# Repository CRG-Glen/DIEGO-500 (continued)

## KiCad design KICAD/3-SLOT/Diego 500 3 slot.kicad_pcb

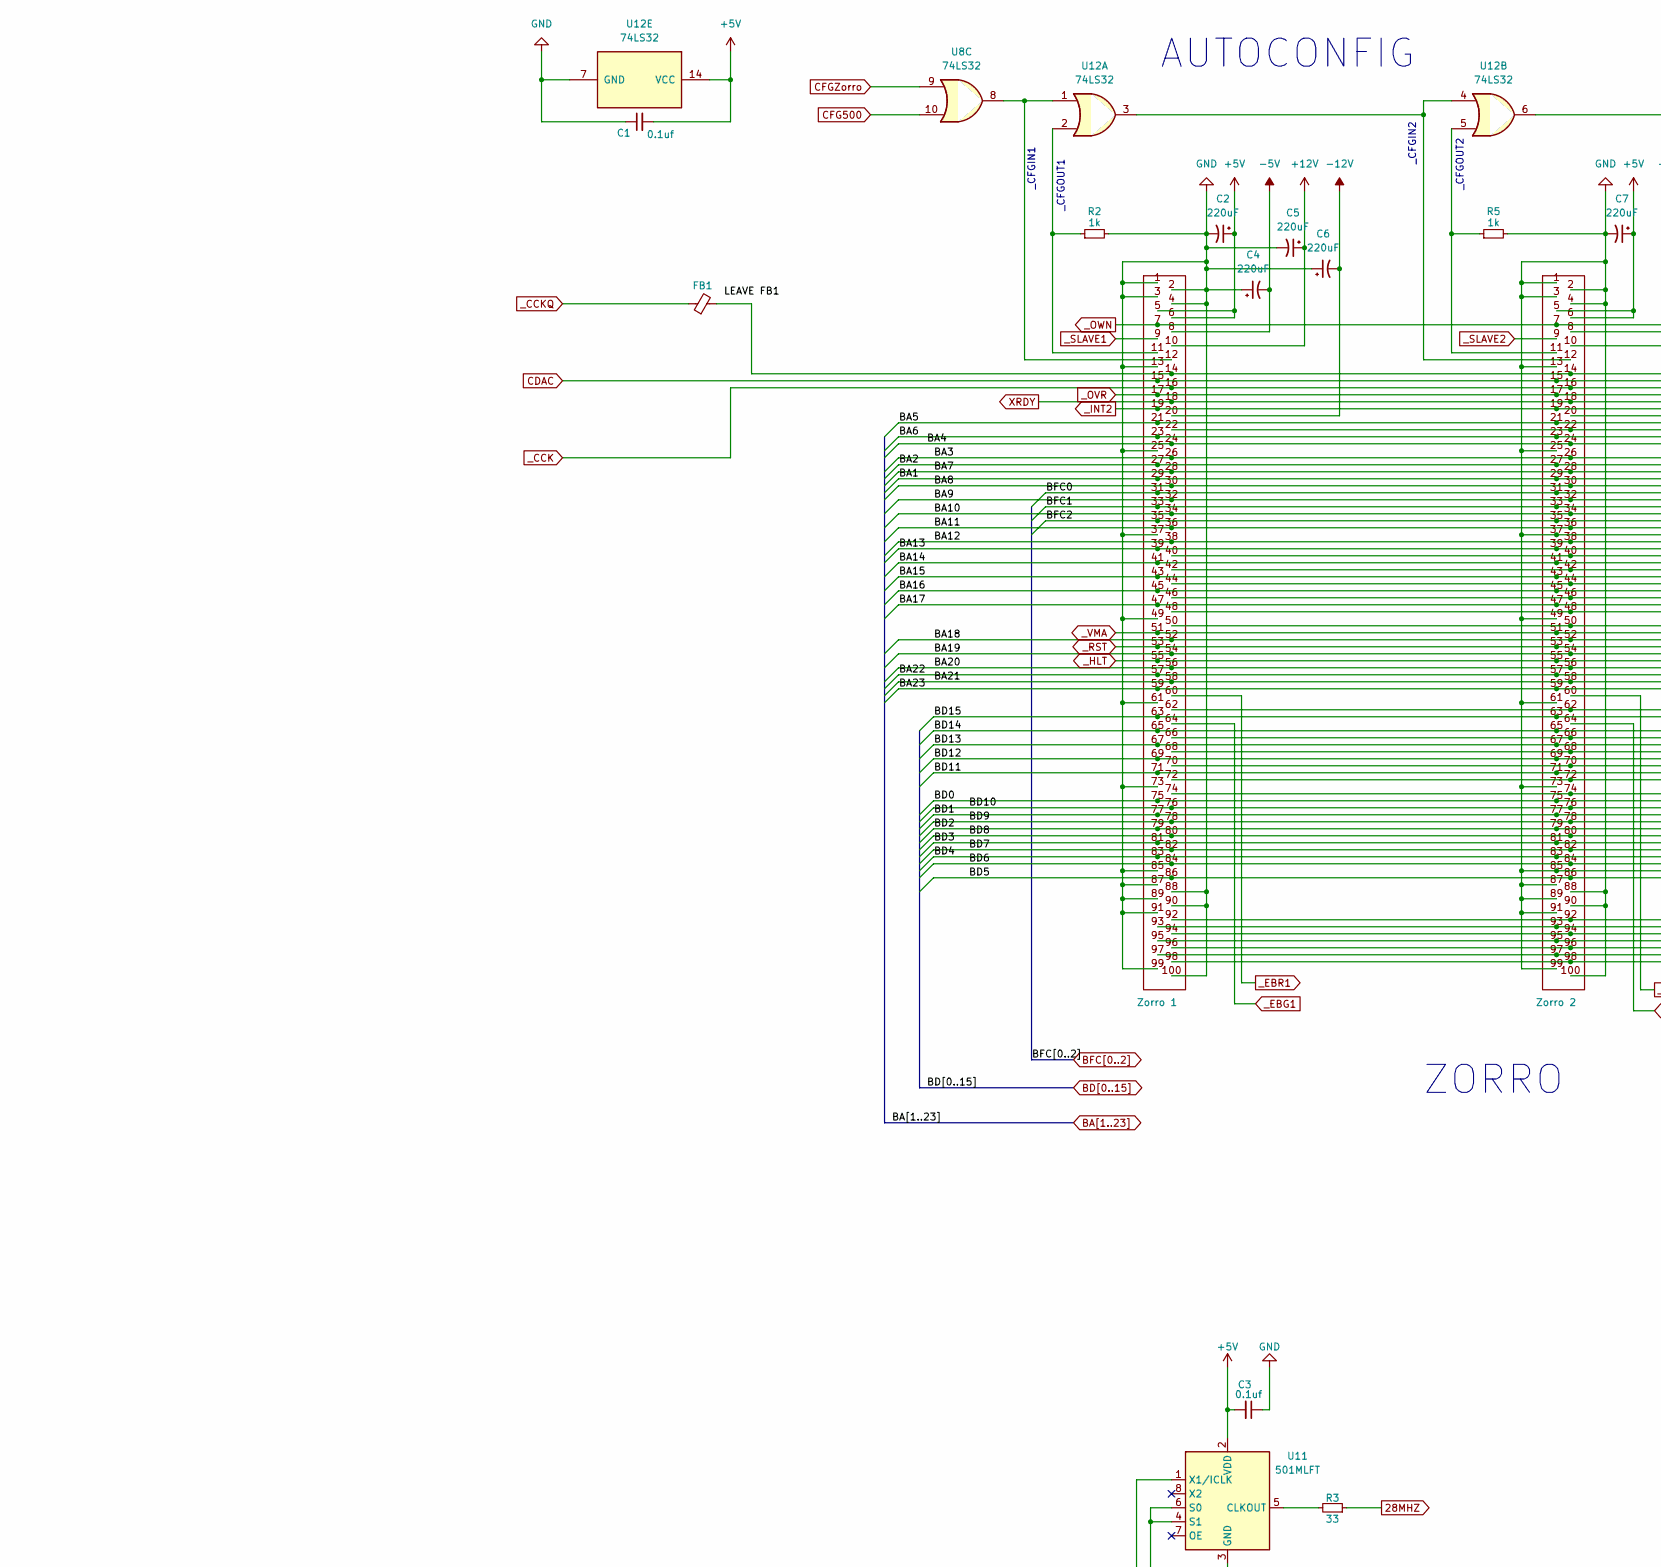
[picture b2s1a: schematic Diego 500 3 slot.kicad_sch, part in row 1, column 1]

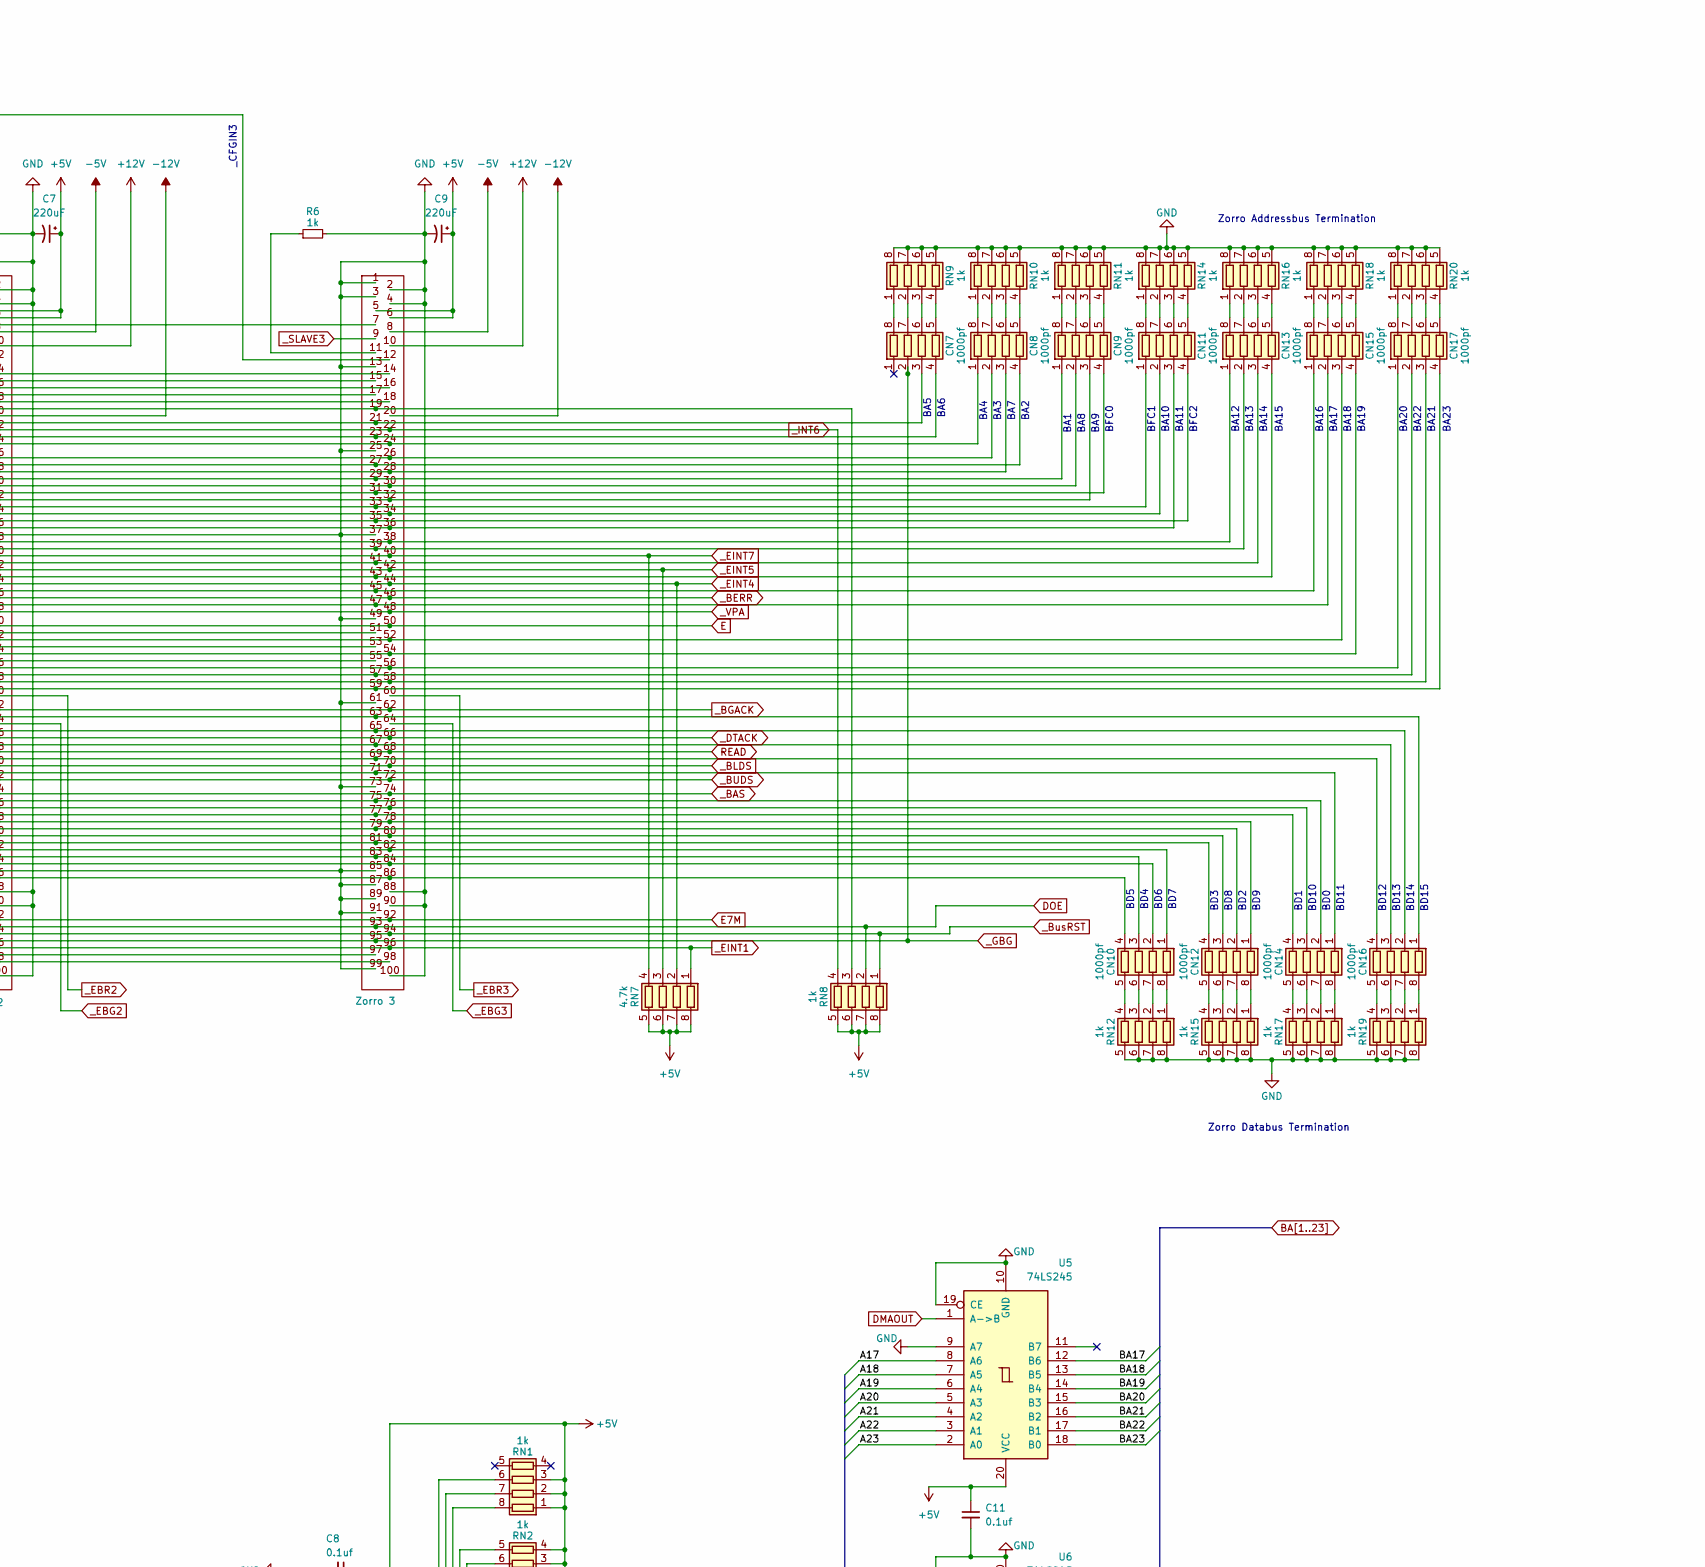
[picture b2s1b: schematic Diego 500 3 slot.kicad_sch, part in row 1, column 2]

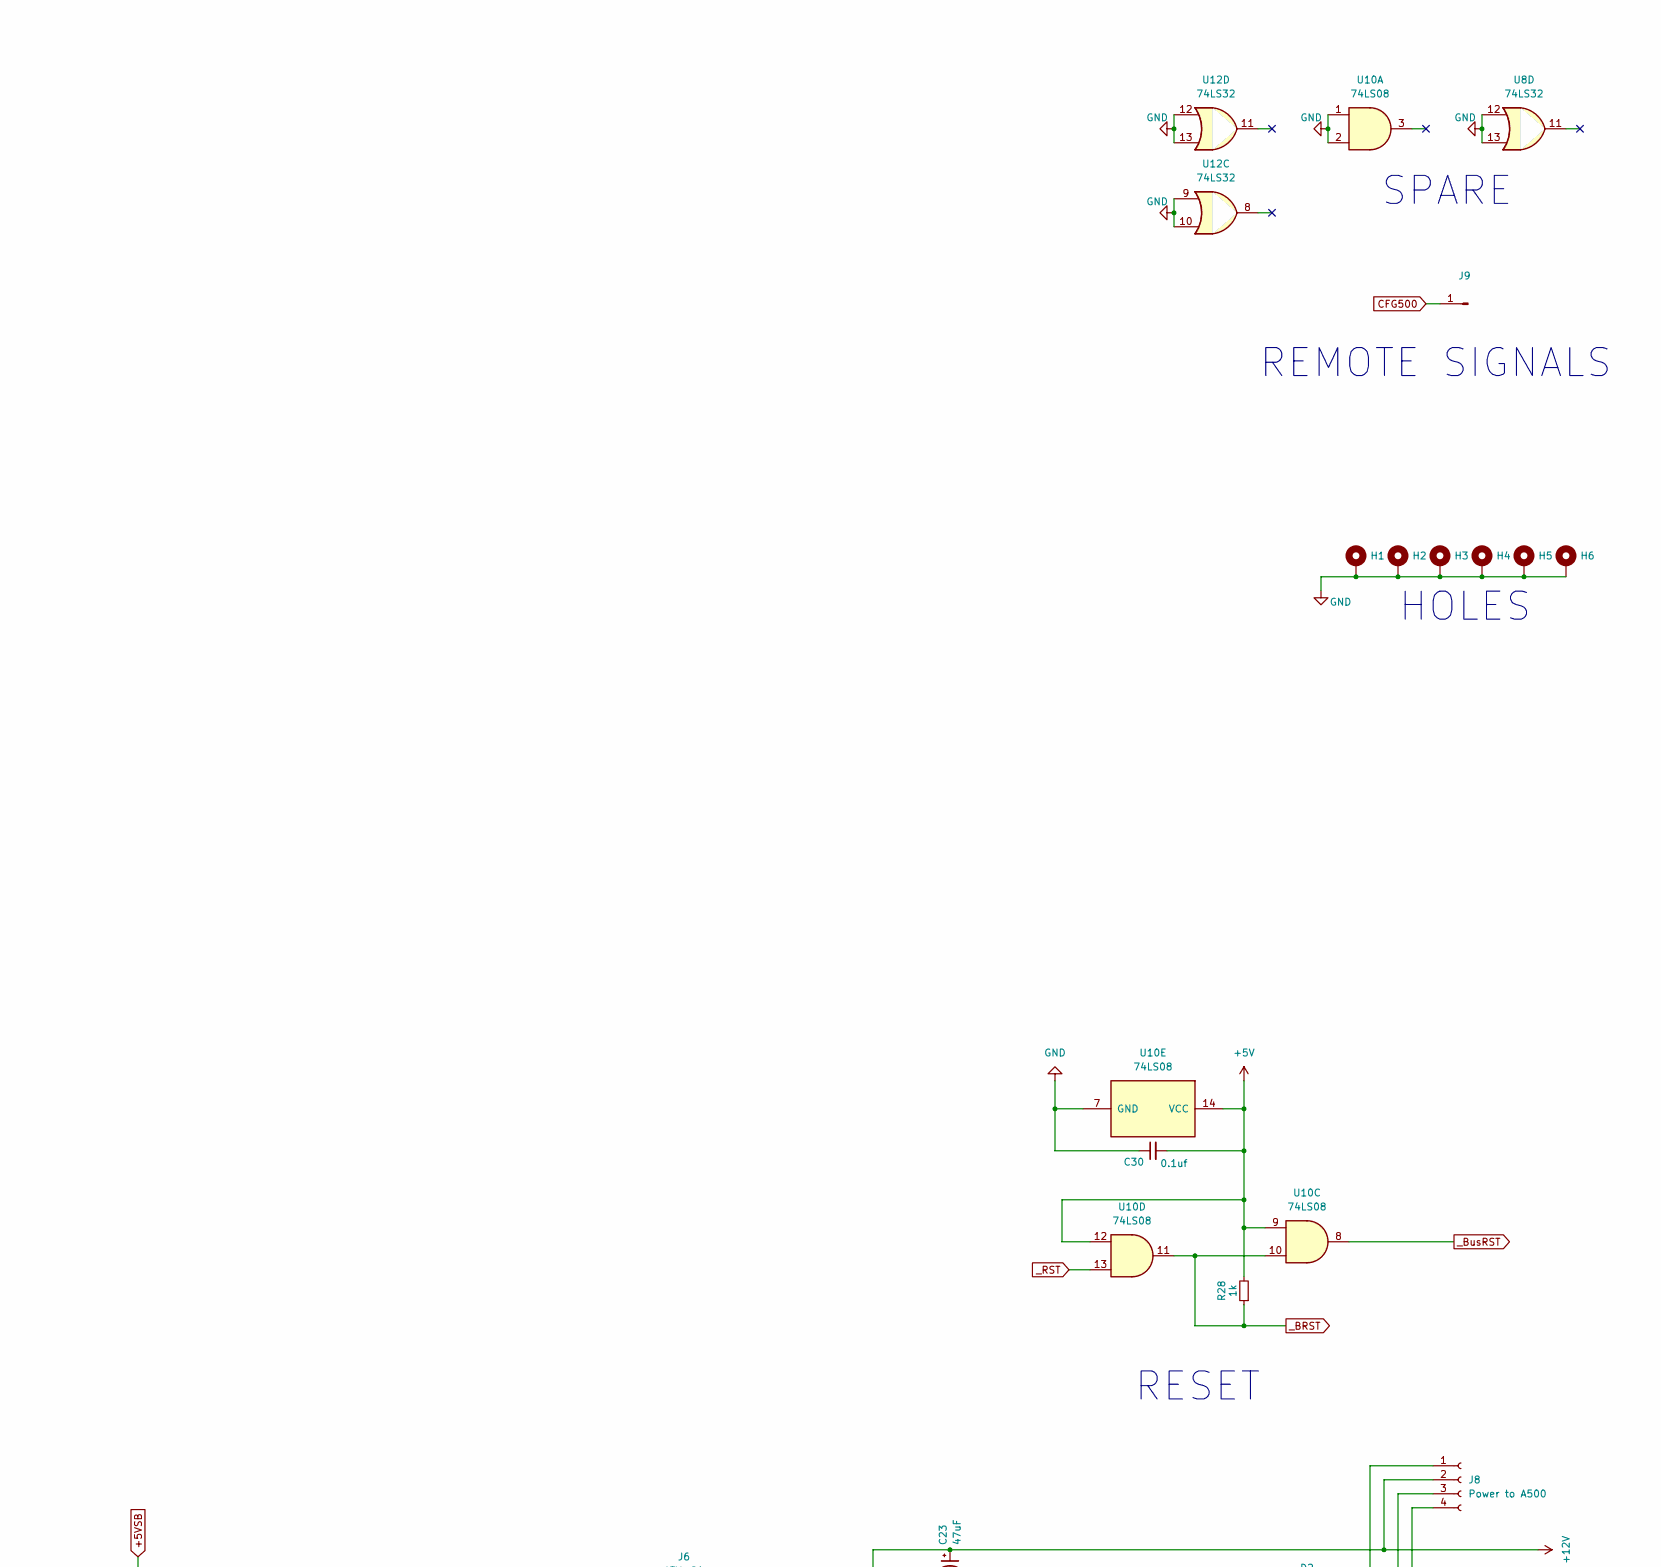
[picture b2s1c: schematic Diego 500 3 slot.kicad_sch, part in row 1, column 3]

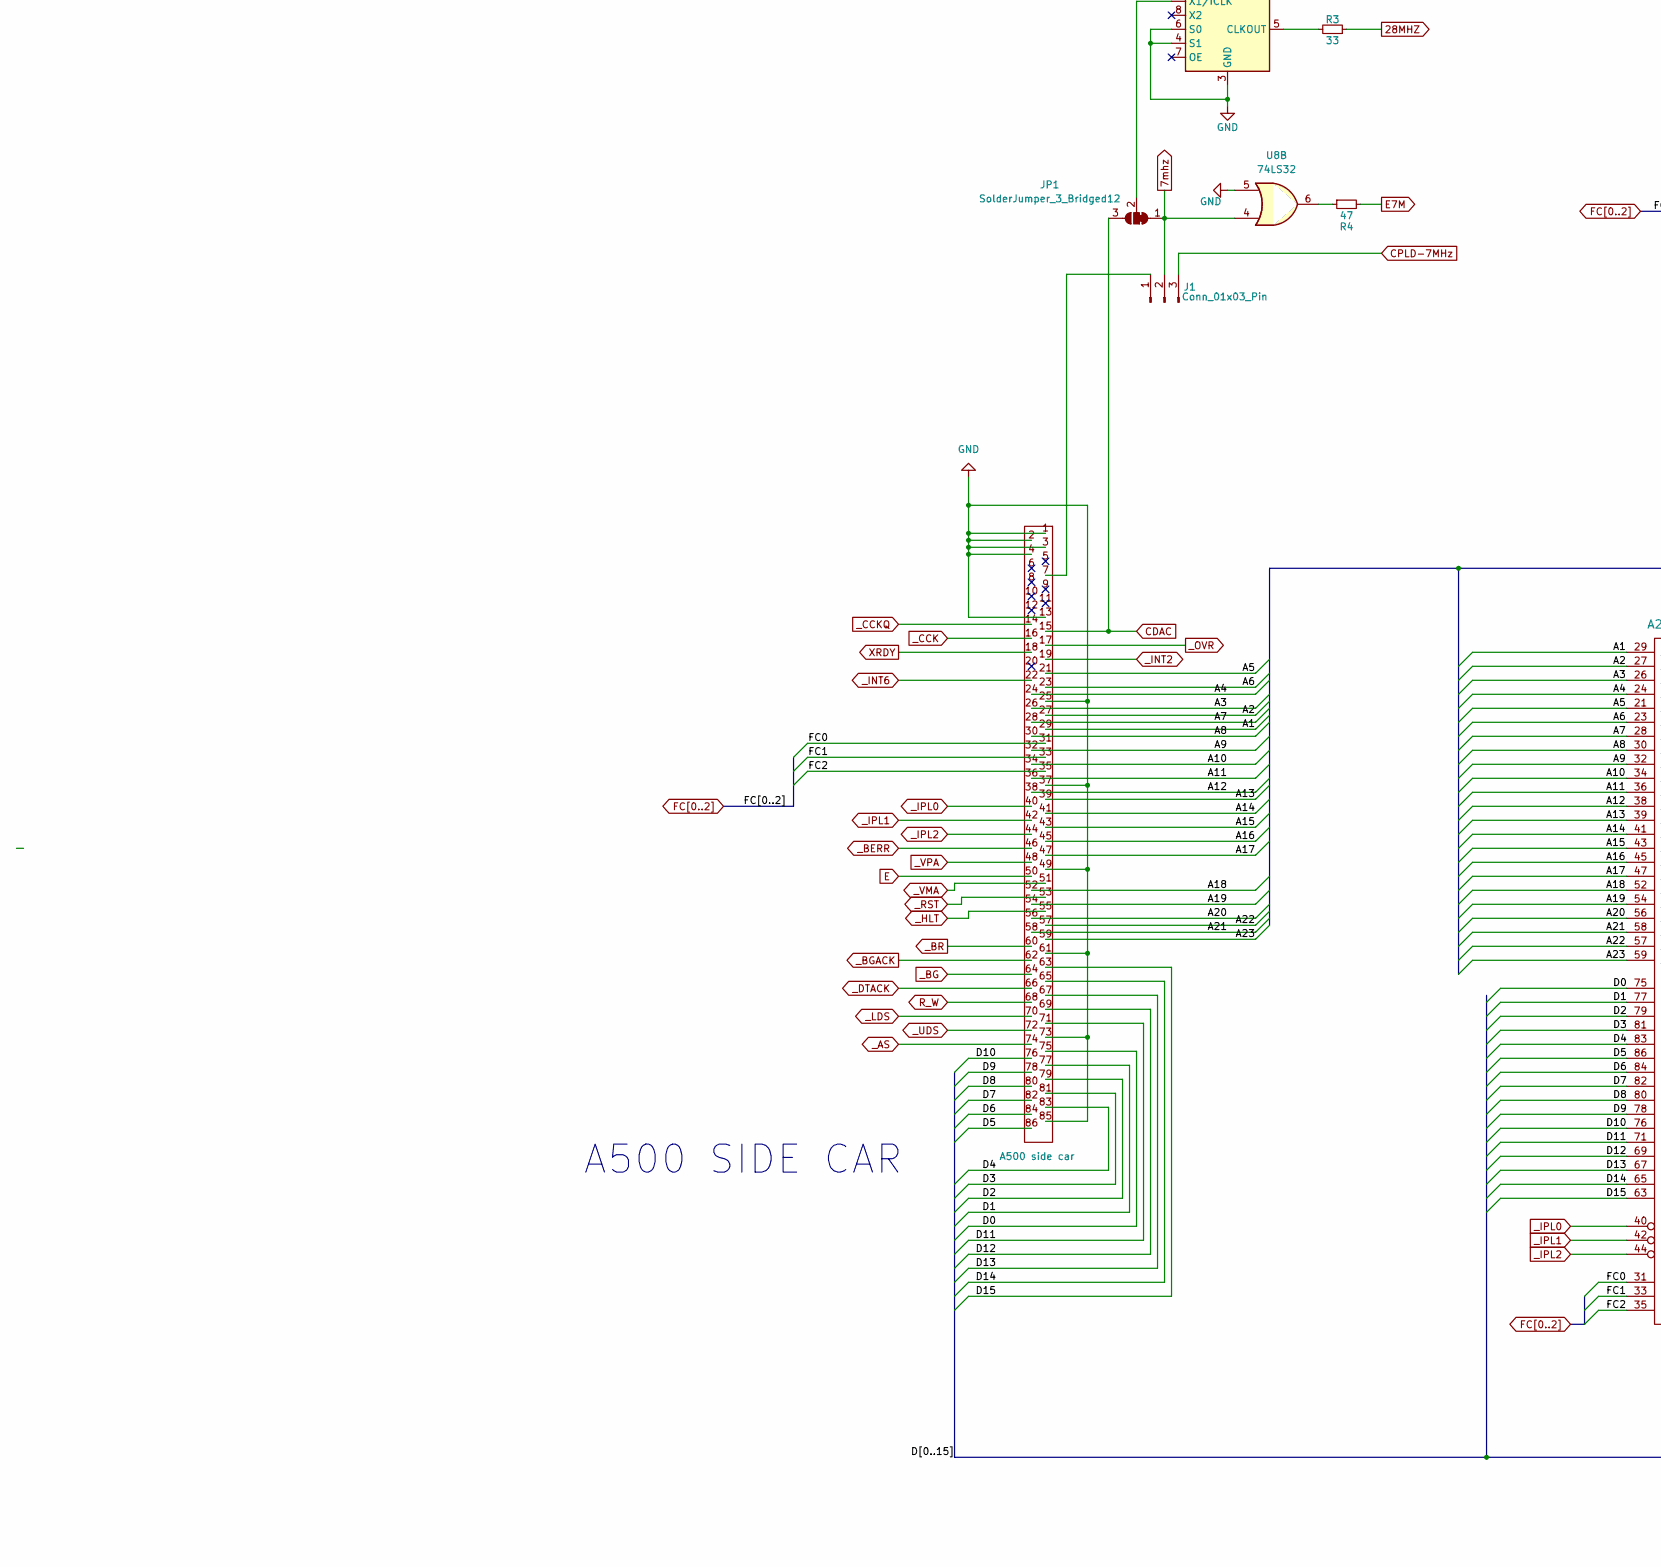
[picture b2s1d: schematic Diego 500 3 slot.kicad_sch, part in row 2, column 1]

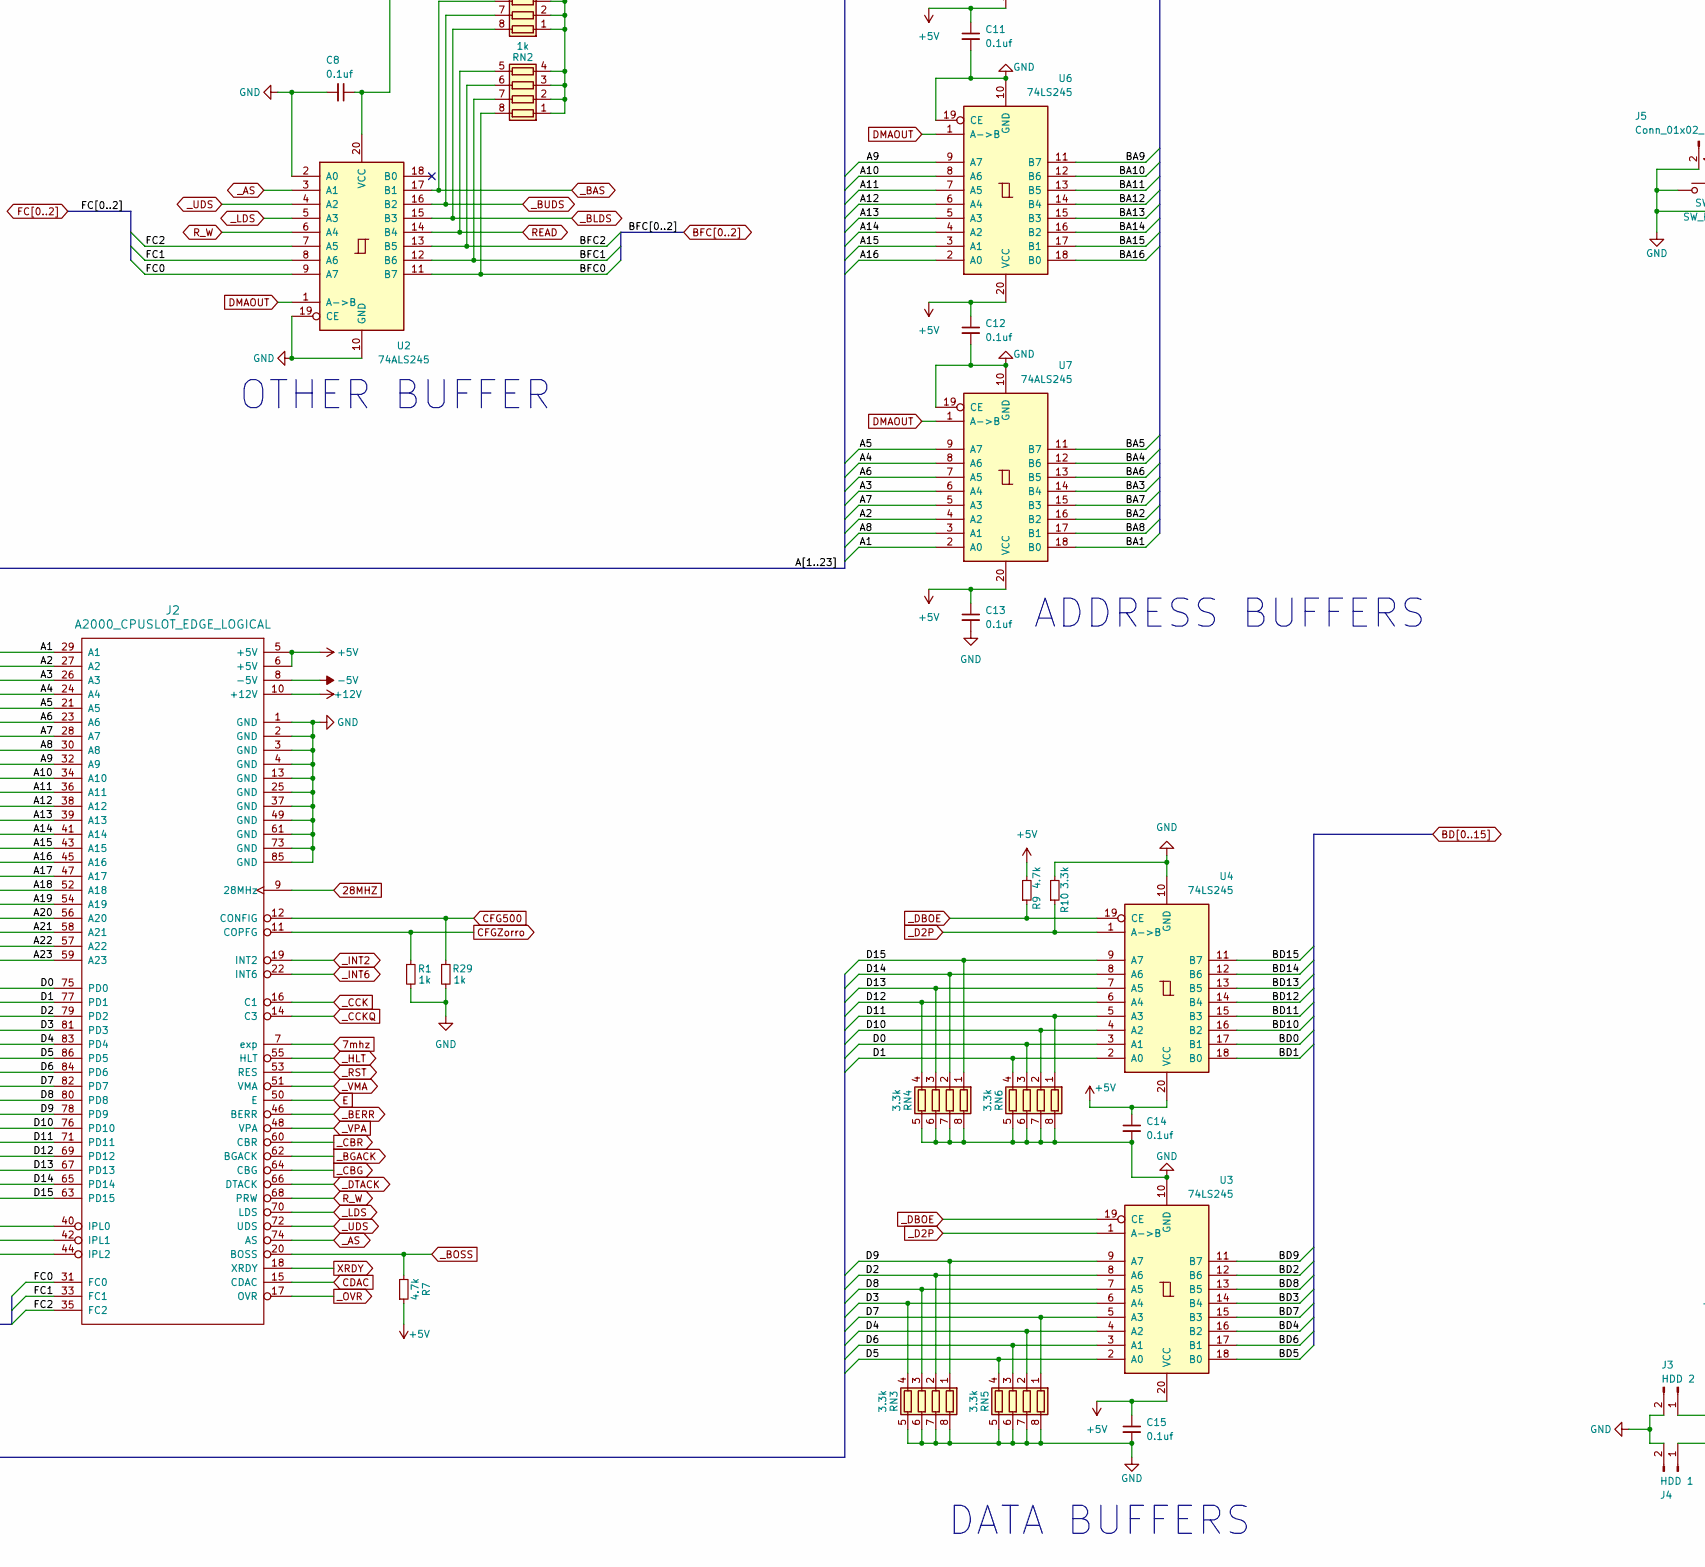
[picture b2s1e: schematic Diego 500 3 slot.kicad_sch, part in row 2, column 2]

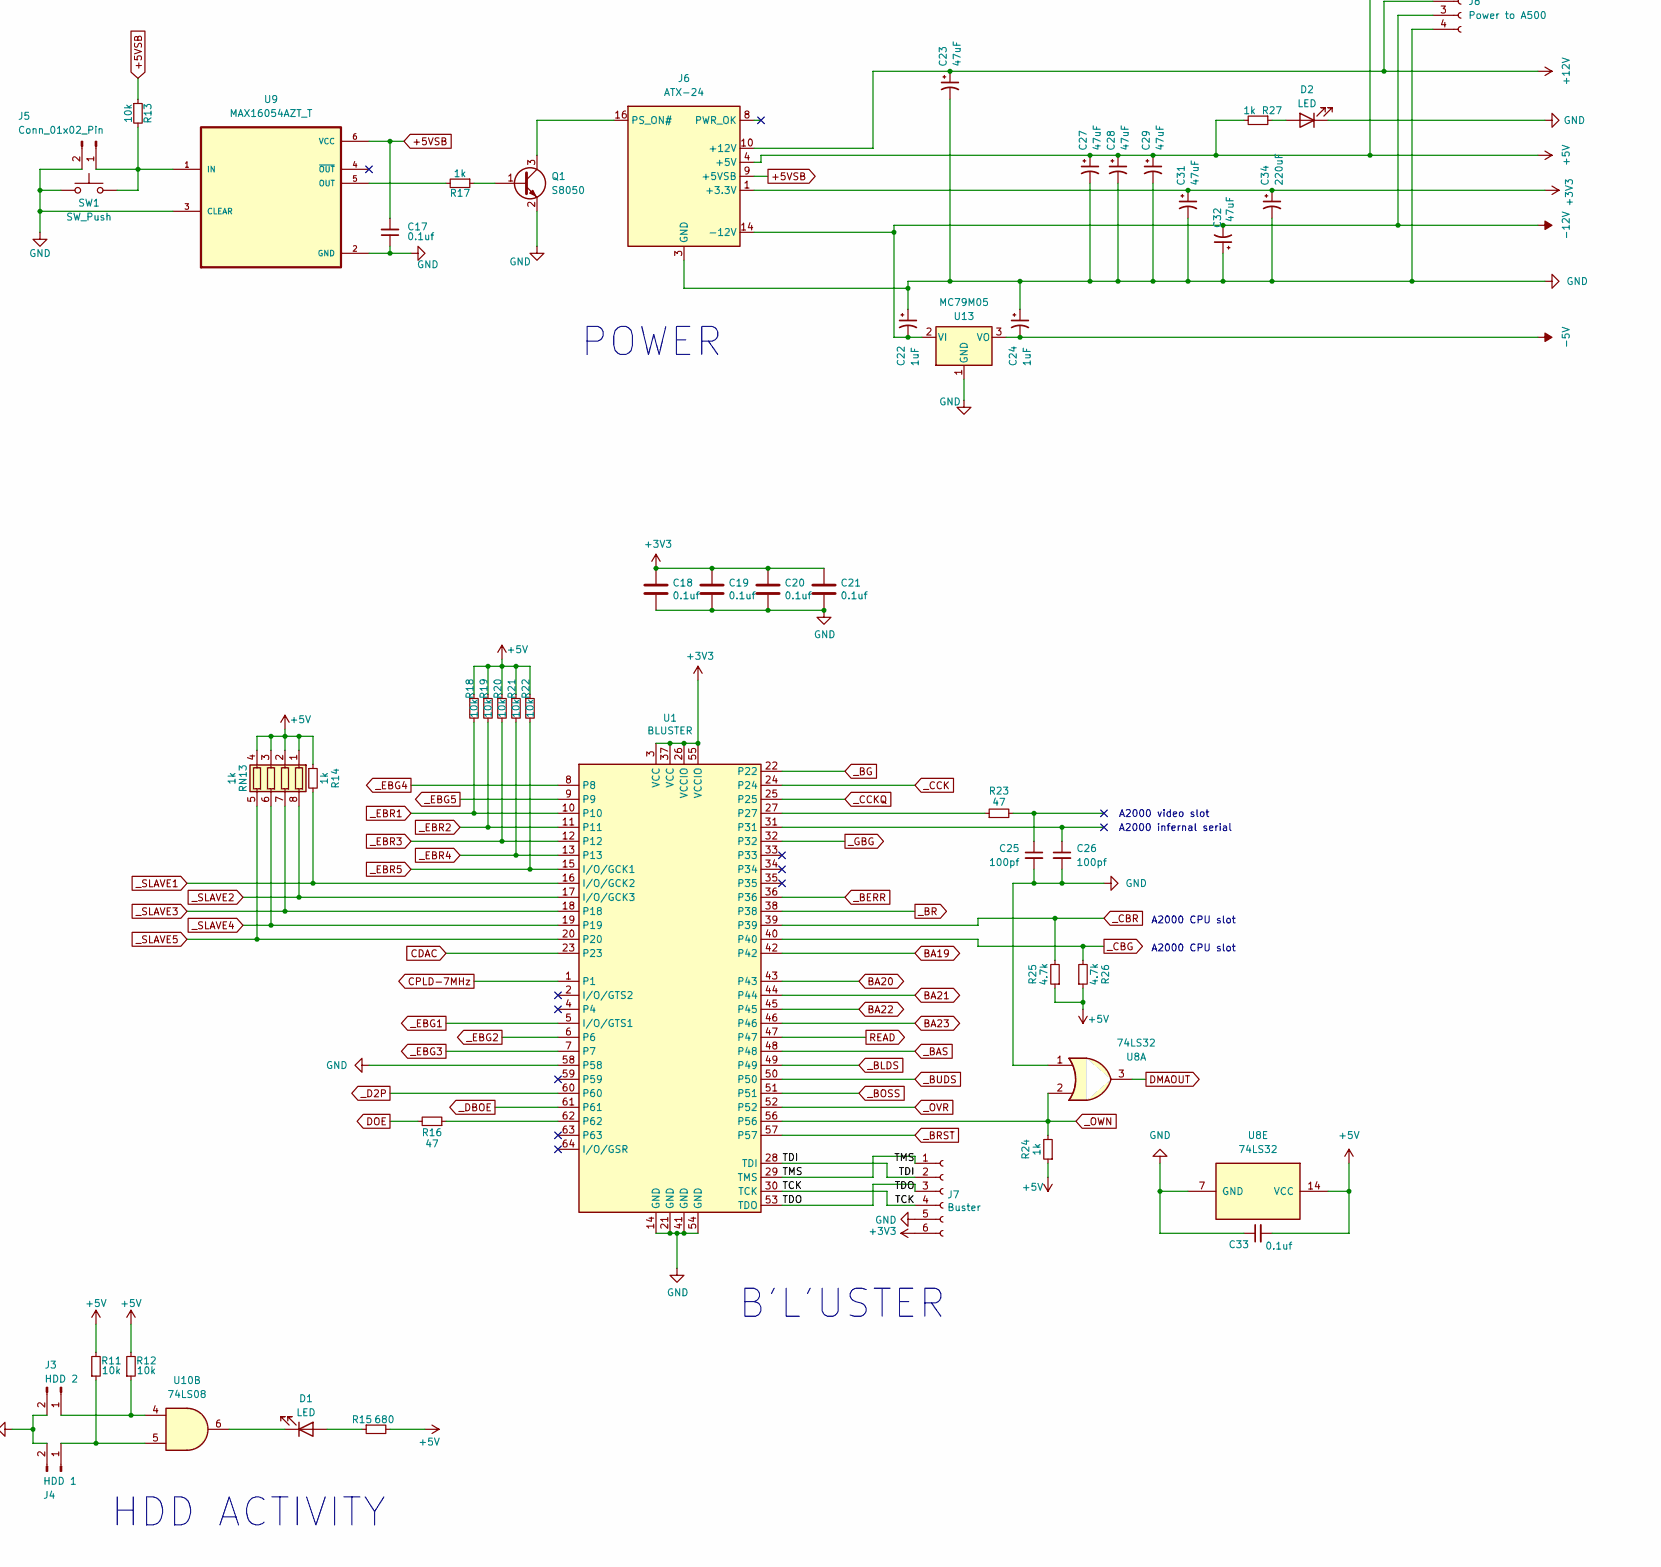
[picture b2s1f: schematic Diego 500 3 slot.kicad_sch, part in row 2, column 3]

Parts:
C1, C3, C8, C11, C12, C13, C14, C15, C17, C30, C33: 0.1uf; C_0805_2012Metric; LCSC C49678
C2, C4, C5, C6, C7, C9, C34: 220uF; CP_Elec_6.3x7.7; LCSC C278407
C18, C19, C20, C21: 0.1uf; C_0805_2012Metric_Pad1.18x1.45mm_HandSolder; LCSC C49678
C22, C24: 1uF; CP_Elec_4x5.4; LCSC C3348
C23, C27, C28, C29, C31, C32: 47uF; CP_Elec_6.3x7.7; LCSC C336249
C25, C26: 100pf; C_0805_2012Metric; LCSC C1790
CN1: A500 side car; A500_SIDE_CONNECTOR
CN2: Zorro 1; Samtec_HLE-150-02-xx-DV-TE_2x50_P2.54mm_Horizontal
CN3: Zorro 2; Samtec_HLE-150-02-xx-DV-TE_2x50_P2.54mm_Horizontal
CN4: Zorro 3; Samtec_HLE-150-02-xx-DV-TE_2x50_P2.54mm_Horizontal
CN7, CN8, CN9, CN10, CN11, CN12, CN13, CN14, CN15, CN16, CN17: 1000pf; R_Array_Convex_4x0603; LCSC C541606
D1: LED; LED_1206_3216Metric_Pad1.42x1.75mm_HandSolder; LCSC C49018
D2: LED; LED_1206_3216Metric_Pad1.42x1.75mm_HandSolder; LCSC C14641
FB1: FerriteBead_Small; D_0805_2012Metric; LCSC C1015
H1, H2, H3, H4, H5, H6: MountingHole_Pad; MountingHole_3.2mm_M3_DIN965_Pad
J1: Conn_01x03_Pin; PinHeader_1x03_P2.54mm_Vertical
J2: A2000_CPUSLOT_EDGE_LOGICAL; Samtec_HLE-150-02-xx-DV-TE_2x43_P2.54mm_Horizontal
J3: HDD 2; PinHeader_1x02_P2.54mm_Vertical
J4: HDD 1; PinHeader_1x02_P2.54mm_Vertical
J5: Conn_01x02_Pin; PinHeader_1x02_P2.54mm_Vertical
J6: ATX-24; Molex_Mini-Fit_Jr_5569-24A2_2x12_P4.20mm_Horizontal
J7: Buster; PinHeader_1x06_P2.54mm_Vertical
J8: Power to A500; Molex_Mini-Fit_Jr_5569-04A2_2x02_P4.20mm_Horizontal
J9: Conn_01x01_Pin; PinHeader_1x01_P2.54mm_Vertical
JP1: SolderJumper_3_Bridged12; SolderJumper-3_P1.3mm_Bridged12_RoundedPad1.0x1.5mm
Q1: S8050; SOT-23; LCSC C2146
R1, R2, R5, R6, R14, R17, R24, R28, R29: 1k; R_0805_2012Metric; LCSC C17513
R3: 33; R_0805_2012Metric; LCSC C17634
R4, R16, R23: 47; R_0805_2012Metric; LCSC C17714
R7, R9, R25, R26: 4.7k; R_0805_2012Metric; LCSC C17673
R10: 3.3k; R_0805_2012Metric; LCSC C26010
R11, R12, R13, R18, R19, R20, R21, R22: 10k; R_0805_2012Metric; LCSC C17414
R15: 680; R_0805_2012Metric; LCSC C17798
R27: 1k; R_0805_2012Metric; LCSC C17798
RN1, RN2, RN8, RN9, RN10, RN11, RN12, RN13, RN14, RN15, RN16, RN17, RN18, RN19, RN20: 1k; R_Array_Convex_4x0603; LCSC C20197
RN3, RN4, RN5, RN6: 3.3k; R_Array_Convex_4x0603; LCSC C102665
RN7: 4.7k; R_Array_Convex_4x0603; LCSC C66697
SW1: SW_Push; SW_PUSH_1P1T_6x3.5mm_H4.3_APEM_MJTP1243
U1: BLUSTER; TQFP-64_10x10mm_P0.5mm; LCSC C90569
U2, U7: 74ALS245; SO-20_5.3x12.6mm_P1.27mm; LCSC C2675885
U3, U4, U5, U6: 74LS245; SO-20_5.3x12.6mm_P1.27mm; LCSC C7753
U8, U12: 74LS32; SO-14_3.9x8.65mm_P1.27mm; LCSC C116812
U9: MAX16054AZT_T; SOT95P275X110-6N; LCSC C79401
U10: 74LS08; SO-14_3.9x8.65mm_P1.27mm; LCSC C6802
U11: 501MLFT; SOIC-8_3.9x4.9mm_P1.27mm; LCSC C2651221
U13: MC79M05; TO-252-2; LCSC C126401

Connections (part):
7mhz: J1.2, J2.7 (exp), JP1.1 (A), U8.4
28MHZ: J2.9 (28MHz), R3.1
+3V3: C18.1, C19.1, C20.1, C21.1, C31.1, C34.1, J6.1 (+3.3V), J6.2 (+3.3V), J6.12 (+3.3V), J6.13 (+3.3V), J7.6, U1.3 (VCC), U1.26 (VCCIO), U1.37 (VCC), U1.55 (VCCIO)
+5V: C1.2, C2.1, C3.2, C7.1, C8.1, C9.1, C11.1, C12.1, C13.1, C14.1, C15.1, C27.1, C28.1, C29.1, C30.2, C33.2, CN2.5, CN2.6, CN3.5, CN3.6, CN4.5, CN4.6, J2.5 (+5V), J2.6 (+5V), J6.4 (+5V), J6.6 (+5V), J6.21 (+5V), J6.22 (+5V), J6.23 (+5V), J8.1, R7.1, R9.2, R11.2, R12.2, R14.1, R15.2, R18.1, R19.1, R20.1, R21.1, R22.1, R24.1, R25.1, R26.1, R27.2, R28.2, RN1.1 (R1.1), RN1.2 (R2.1), RN1.3 (R3.1), RN2.1 (R1.1), RN2.2 (R2.1), RN2.3 (R3.1), RN2.4 (R4.1), RN7.5 (R4.2), RN7.6 (R3.2), RN7.7 (R2.2), RN7.8 (R1.2), RN8.5 (R4.2), RN8.6 (R3.2), RN8.7 (R2.2), RN8.8 (R1.2), RN13.1 (R1.1), RN13.2 (R2.1), RN13.3 (R3.1), RN13.4 (R4.1), U2.20 (VCC), U3.20 (VCC), U4.20 (VCC), U5.20 (VCC), U6.20 (VCC), U7.20 (VCC), U8.14 (VCC), U10.9, U10.12, U10.14 (VCC), U11.2 (VDD), U12.14 (VCC); also elsewhere on the board
+5VSB: C17.2, J6.9 (+5VSB), R13.1, U9.6 (VCC)
+12V: C5.1, C23.1, CN2.10, CN3.10, CN4.10, J2.10 (+12V), J6.10 (+12V), J6.11 (+12V), J8.2
-5V: C4.2, C24.2, CN2.8, CN3.8, CN4.8, J2.8 (-5V), U13.3 (VO)
-12V: C6.2, C22.2, C32.2, CN2.20, CN3.20, CN4.20, J6.14 (-12V), J8.3, U13.2 (VI)
/A1: CN1.29, J2.29 (A1), U7.2 (A0)
/A2: CN1.27, J2.27 (A2), U7.4 (A2)
/A3: CN1.26, J2.26 (A3), U7.6 (A4)
/A4: CN1.24, J2.24 (A4), U7.8 (A6)
/A5: CN1.21, J2.21 (A5), U7.9 (A7)
/A6: CN1.23, J2.23 (A6), U7.7 (A5)
/A7: CN1.28, J2.28 (A7), U7.5 (A3)
/A8: CN1.30, J2.30 (A8), U7.3 (A1)
/A9: CN1.32, J2.32 (A9), U6.9 (A7)
/A10: CN1.34, J2.34 (A10), U6.8 (A6)
/A11: CN1.36, J2.36 (A11), U6.7 (A5)
/A12: CN1.38, J2.38 (A12), U6.6 (A4)
/A13: CN1.39, J2.39 (A13), U6.5 (A3)
/A14: CN1.41, J2.41 (A14), U6.4 (A2)
/A15: CN1.43, J2.43 (A15), U6.3 (A1)
/A16: CN1.45, J2.45 (A16), U6.2 (A0)
/A17: CN1.47, J2.47 (A17), U5.8 (A6)
/A18: CN1.52, J2.52 (A18), U5.7 (A5)
/A19: CN1.54, J2.54 (A19), U5.6 (A4)
/A20: CN1.56, J2.56 (A20), U5.5 (A3)
/A21: CN1.58, J2.58 (A21), U5.4 (A2)
/A22: CN1.57, J2.57 (A22), U5.3 (A1)
/A23: CN1.59, J2.59 (A23), U5.2 (A0)
/D0: CN1.75, J2.75 (PD0), RN6.3 (R3.1), U4.3 (A1)
/D1: CN1.77, J2.77 (PD1), RN6.4 (R4.1), U4.2 (A0)
/D2: CN1.79, J2.79 (PD2), RN3.2 (R2.1), U3.8 (A6)
/D3: CN1.81, J2.81 (PD3), RN3.4 (R4.1), U3.6 (A4)
/D4: CN1.83, J2.83 (PD4), RN5.2 (R2.1), U3.4 (A2)
/D5: CN1.86, J2.86 (PD5), RN5.4 (R4.1), U3.2 (A0)
/D6: CN1.84, J2.84 (PD6), RN5.3 (R3.1), U3.3 (A1)
/D7: CN1.82, J2.82 (PD7), RN5.1 (R1.1), U3.5 (A3)
/D8: CN1.80, J2.80 (PD8), RN3.3 (R3.1), U3.7 (A5)
/D9: CN1.78, J2.78 (PD9), RN3.1 (R1.1), U3.9 (A7)
/D10: CN1.76, J2.76 (PD10), RN6.2 (R2.1), U4.4 (A2)
/D11: CN1.71, J2.71 (PD11), RN6.1 (R1.1), U4.5 (A3)
/D12: CN1.69, J2.69 (PD12), RN4.4 (R4.1), U4.6 (A4)
/D13: CN1.67, J2.67 (PD13), RN4.3 (R3.1), U4.7 (A5)
/D14: CN1.65, J2.65 (PD14), RN4.2 (R2.1), U4.8 (A6)
/D15: CN1.63, J2.63 (PD15), RN4.1 (R1.1), U4.9 (A7)
/TCK: J7.4, U1.30 (TCK)
/TDI: J7.2, U1.28 (TDI)
/TDO: J7.3, U1.53 (TDO)
/TMS: J7.1, U1.29 (TMS)
BA1: CN2.29, CN3.29, CN4.29, CN9.1 (R1.1), U7.18 (B0)
BA2: CN2.27, CN3.27, CN4.27, CN8.4 (R4.1), U7.16 (B2)
BA3: CN2.26, CN3.26, CN4.26, CN8.2 (R2.1), U7.14 (B4)
BA4: CN2.24, CN3.24, CN4.24, CN8.1 (R1.1), U7.12 (B6)
BA5: CN2.21, CN3.21, CN4.21, CN7.3 (R3.1), U7.11 (B7)
BA6: CN2.23, CN3.23, CN4.23, CN7.4 (R4.1), U7.13 (B5)
BA7: CN2.28, CN3.28, CN4.28, CN8.3 (R3.1), U7.15 (B3)
BA8: CN2.30, CN3.30, CN4.30, CN9.2 (R2.1), U7.17 (B1)
BA9: CN2.32, CN3.32, CN4.32, CN9.3 (R3.1), U6.11 (B7)
BA10: CN2.34, CN3.34, CN4.34, CN11.2 (R2.1), U6.12 (B6)
BA11: CN2.36, CN3.36, CN4.36, CN11.3 (R3.1), U6.13 (B5)
BA12: CN2.38, CN3.38, CN4.38, CN13.1 (R1.1), U6.14 (B4)
BA13: CN2.39, CN3.39, CN4.39, CN13.2 (R2.1), U6.15 (B3)
BA14: CN2.41, CN3.41, CN4.41, CN13.3 (R3.1), U6.16 (B2)
BA15: CN2.43, CN3.43, CN4.43, CN13.4 (R4.1), U6.17 (B1)
BA16: CN2.45, CN3.45, CN4.45, CN15.1 (R1.1), U6.18 (B0)
BA17: CN2.47, CN3.47, CN4.47, CN15.2 (R2.1), U5.12 (B6)
BA18: CN2.52, CN3.52, CN4.52, CN15.3 (R3.1), U5.13 (B5)
BA19: CN2.54, CN3.54, CN4.54, CN15.4 (R4.1), U1.42, U5.14 (B4)
BA20: CN2.56, CN3.56, CN4.56, CN17.1 (R1.1), U1.43, U5.15 (B3)
BA21: CN2.58, CN3.58, CN4.58, CN17.3 (R3.1), U1.44, U5.16 (B2)
BA22: CN2.57, CN3.57, CN4.57, CN17.2 (R2.1), U1.45, U5.17 (B1)
BA23: CN2.59, CN3.59, CN4.59, CN17.4 (R4.1), U1.46, U5.18 (B0)
BD0: CN2.75, CN3.75, CN4.75, CN14.2 (R2.1), U4.17 (B1)
BD1: CN2.77, CN3.77, CN4.77, CN14.4 (R4.1), U4.18 (B0)
BD2: CN2.79, CN3.79, CN4.79, CN12.2 (R2.1), U3.12 (B6)
BD3: CN2.81, CN3.81, CN4.81, CN12.4 (R4.1), U3.14 (B4)
BD4: CN2.83, CN3.83, CN4.83, CN10.3 (R3.1), U3.16 (B2)
BD5: CN2.86, CN3.86, CN4.86, CN10.4 (R4.1), U3.18 (B0)
BD6: CN2.84, CN3.84, CN4.84, CN10.2 (R2.1), U3.17 (B1)
BD7: CN2.82, CN3.82, CN4.82, CN10.1 (R1.1), U3.15 (B3)
BD8: CN2.80, CN3.80, CN4.80, CN12.3 (R3.1), U3.13 (B5)
BD9: CN2.78, CN3.78, CN4.78, CN12.1 (R1.1), U3.11 (B7)
BD10: CN2.76, CN3.76, CN4.76, CN14.3 (R3.1), U4.16 (B2)
BD11: CN2.71, CN3.71, CN4.71, CN14.1 (R1.1), U4.15 (B3)
BD12: CN2.69, CN3.69, CN4.69, CN16.4 (R4.1), U4.14 (B4)
BD13: CN2.67, CN3.67, CN4.67, CN16.3 (R3.1), U4.13 (B5)
BD14: CN2.65, CN3.65, CN4.65, CN16.2 (R2.1), U4.12 (B6)
BD15: CN2.63, CN3.63, CN4.63, CN16.1 (R1.1), U4.11 (B7)
BFC0: CN2.31, CN3.31, CN4.31, CN9.4 (R4.1), RN2.8 (R1.2), U2.11 (B7)
BFC1: CN2.33, CN3.33, CN4.33, CN11.1 (R1.1), RN2.7 (R2.2), U2.12 (B6)
BFC2: CN2.35, CN3.35, CN4.35, CN11.4 (R4.1), RN2.6 (R3.2), U2.13 (B5)
CDAC: CN1.15, CN2.15, CN3.15, CN4.15, J2.15 (CDAC), JP1.3 (B), U1.23
CFG500: J2.12 (CONFIG), J9.1, R29.1, U8.10
CFGZorro: J2.11 (COPFG), R1.1, U8.9
CPLD-7MHz: J1.3, U1.1
DMAOUT: U2.1 (A->B), U5.1 (A->B), U6.1 (A->B), U7.1 (A->B), U8.3
DOE: CN2.93, CN3.93, CN4.93, R16.2, RN8.2 (R2.1); also elsewhere on the board
E: CN1.50, CN2.50, CN3.50, CN4.50, J2.50 (E)
E7M: CN2.92, CN3.92, CN4.92, R4.2
FC0: CN1.31, J2.31 (FC0), U2.9 (A7)
FC1: CN1.33, J2.33 (FC1), U2.8 (A6)
FC2: CN1.35, J2.35 (FC2), U2.7 (A5)
GND: C1.1, C2.2, C3.1, C4.1, C5.2, C6.1, C7.2, C8.2, C9.2, C11.2, C12.2, C13.2, C14.2, C15.2, C17.1, C18.2, C19.2, C20.2, C21.2, C22.1, C23.2, C24.1, C25.2, C26.2, C27.2, C28.2, C29.2, C30.1, C31.2, C32.1, C33.1, C34.2, CN1.1, CN1.2, CN1.3, CN1.4, CN1.13, CN1.25, CN1.37, CN1.49, CN1.61, CN1.73, CN1.85, CN2.1, CN2.2, CN2.3, CN2.4, CN2.13, CN2.25, CN2.37, CN2.49, CN2.61, CN2.73, CN2.85, CN2.87, CN2.88, CN2.89, CN2.90, CN2.91, CN2.99, CN2.100, CN3.1, CN3.2, CN3.3, CN3.4, CN3.13, CN3.25, CN3.37, CN3.49, CN3.61, CN3.73, CN3.85, CN3.87, CN3.88, CN3.89, CN3.90, CN3.91, CN3.99, CN3.100, CN4.1, CN4.2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
unnamed: CN2.11, R2.1, U12.2
unnamed: CN2.12, U8.8, U12.1
unnamed: CN2.14, CN3.14, CN4.14, FB1.2
unnamed: CN2.97, CN3.97, CN4.97
unnamed: CN2.98, CN3.98, CN4.98
unnamed: CN3.11, R5.1, U12.5
unnamed: CN3.12, U12.3, U12.4
unnamed: CN4.11, R6.1
unnamed: CN4.12, U12.6
unnamed: CN7.8 (R1.2), RN9.1 (R1.1)
unnamed: CN7.7 (R2.2), RN9.2 (R2.1)
unnamed: CN7.6 (R3.2), RN9.3 (R3.1)
unnamed: CN7.5 (R4.2), RN9.4 (R4.1)
unnamed: CN8.8 (R1.2), RN10.1 (R1.1)
unnamed: CN8.7 (R2.2), RN10.2 (R2.1)
unnamed: CN8.6 (R3.2), RN10.3 (R3.1)
unnamed: CN8.5 (R4.2), RN10.4 (R4.1)
unnamed: CN9.8 (R1.2), RN11.1 (R1.1)
unnamed: CN9.7 (R2.2), RN11.2 (R2.1)
unnamed: CN9.6 (R3.2), RN11.3 (R3.1)
unnamed: CN9.5 (R4.2), RN11.4 (R4.1)
unnamed: CN10.8 (R1.2), RN12.1 (R1.1)
unnamed: CN10.7 (R2.2), RN12.2 (R2.1)
unnamed: CN10.6 (R3.2), RN12.3 (R3.1)
unnamed: CN10.5 (R4.2), RN12.4 (R4.1)
unnamed: CN11.8 (R1.2), RN14.1 (R1.1)
unnamed: CN11.7 (R2.2), RN14.2 (R2.1)
unnamed: CN11.6 (R3.2), RN14.3 (R3.1)
unnamed: CN11.5 (R4.2), RN14.4 (R4.1)
unnamed: CN12.8 (R1.2), RN15.1 (R1.1)
unnamed: CN12.7 (R2.2), RN15.2 (R2.1)
unnamed: CN12.6 (R3.2), RN15.3 (R3.1)
unnamed: CN12.5 (R4.2), RN15.4 (R4.1)
unnamed: CN13.8 (R1.2), RN16.1 (R1.1)
unnamed: CN13.7 (R2.2), RN16.2 (R2.1)
unnamed: CN13.6 (R3.2), RN16.3 (R3.1)
unnamed: CN13.5 (R4.2), RN16.4 (R4.1)
unnamed: CN14.8 (R1.2), RN17.1 (R1.1)
unnamed: CN14.7 (R2.2), RN17.2 (R2.1)
unnamed: CN14.6 (R3.2), RN17.3 (R3.1)
unnamed: CN14.5 (R4.2), RN17.4 (R4.1)
unnamed: CN15.8 (R1.2), RN18.1 (R1.1)
unnamed: CN15.7 (R2.2), RN18.2 (R2.1)
unnamed: CN15.6 (R3.2), RN18.3 (R3.1)
unnamed: CN15.5 (R4.2), RN18.4 (R4.1)
unnamed: CN16.8 (R1.2), RN19.1 (R1.1)
unnamed: CN16.7 (R2.2), RN19.2 (R2.1)
unnamed: CN16.6 (R3.2), RN19.3 (R3.1)
unnamed: CN16.5 (R4.2), RN19.4 (R4.1)
unnamed: CN17.8 (R1.2), RN20.1 (R1.1)
unnamed: CN17.7 (R2.2), RN20.2 (R2.1)
unnamed: CN17.6 (R3.2), RN20.3 (R3.1)
unnamed: CN17.5 (R4.2), RN20.4 (R4.1)
unnamed: D1.2 (A), R15.1
unnamed: D1.1 (K), U10.6
unnamed: D2.2 (A), R27.1
unnamed: CN1.7, J1.1
unnamed: J3.1, R12.1, U10.4
unnamed: J4.1, R11.1, U10.5
unnamed: J5.1, R13.2, SW1.2, U9.1 (IN)
unnamed: J6.16 (PS_ON#), Q1.3 (C)
unnamed: JP1.2 (C), U11.1 (X1/ICLK)
unnamed: Q1.1 (B), R17.1
unnamed: R4.1, U8.6
unnamed: R23.1, U1.27
unnamed: R16.1, U1.62
unnamed: R17.2, U9.5 (OUT)
unnamed: R3.2, U11.5 (CLKOUT)
READ: CN2.68, CN3.68, CN4.68, RN2.5 (R4.2), U1.47, U2.14 (B4)
R_W: CN1.68, J2.68 (PRW), U2.6 (A4)
XRDY: CN1.18, CN2.18, CN3.18, CN4.18, J2.18 (XRDY)
_AS: CN1.74, J2.74 (AS), U2.3 (A1)
_BAS: CN2.74, CN3.74, CN4.74, RN1.6 (R3.2), U1.48, U2.17 (B1)
_BERR: CN1.46, CN2.46, CN3.46, CN4.46, J2.46 (BERR), U1.36
_BG: CN1.64, U1.22
_BGACK: CN1.62, CN2.62, CN3.62, CN4.62, J2.62 (BGACK)
_BLDS: CN2.70, CN3.70, CN4.70, RN1.8 (R1.2), U1.49, U2.15 (B3)
_BOSS: J2.20 (BOSS), R7.2, U1.51
_BR: CN1.60, U1.38
_BRST: R28.1, U1.57, U10.10, U10.11
_BUDS: CN2.72, CN3.72, CN4.72, RN1.7 (R2.2), U1.50, U2.16 (B2)
_BusRST: CN2.94, CN3.94, CN4.94, RN8.1 (R1.1), U10.8; also elsewhere on the board
_CBG: J2.64 (CBG), R26.2, U1.40
_CBR: J2.60 (CBR), R25.2, U1.39
_CCK: CN1.16, CN2.16, CN3.16, CN4.16, J2.16 (C1), U1.24
_CCKQ: CN1.14, FB1.1, J2.14 (C3), U1.25
_D2P: R10.1, U1.60, U3.1 (A->B), U4.1 (A->B)
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
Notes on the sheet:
_CFGIN2
BA11
Zorro Addressbus Termination
AUTOCONFIG
BA18
BD14
BD15
BD1
BD4
BD11
BD9
BD6
BA1
BA3
BD2
BA21
BD13
BA16
BA15
BD0
BA20
POWER
OTHER BUFFER
SPARE
BA8
BD7
BA2
HDD ACTIVITY
BFC0
REMOTE SIGNALS
BA23
BA5
BA22
BD8
BA4
A2000 video slot
RESET
BD5
BA6
BA9
